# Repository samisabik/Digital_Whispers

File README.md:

## Digital Whispers

In a world populated by an increasing abundance of Artificial Intelligences (AI), it has become more and more important for us to understand the behaviours of our smarter machines. AI promises perfect systems designed to master their functions. As humans, we have imbued these artificial creatures with senses. We have given them the ability to communicate to an ever nearer degree of naturalness; speech and hearing being the most developed. With these efforts, we expect these systems to be as perfect as we have designed them; but what about errors? Beautiful mispronunciation? Hearing loss? Faded meaning? What about the little misunderstandings that makes us human? Can a machine suffer from them and experience them also?

Digital Whispers is an installation that sets seven computers and one human in to a game of Chinese Whispers. The visitor inputs the seed sentence into the “ear” of the first computer and the dialog of ethereal whispers continues in a chain until every machine has had its say. Each computer can hear and talk. It whispers to its neighbour the sentence as it comes into its “ears”. Errors evolves involuntary (or not), creating word chimeras, often resulting in absurd sentences only a robot could have created. The final phrase spoken back to the visitor, most often with surreal overtones, leaves to question the machine as a reflection of humanity.

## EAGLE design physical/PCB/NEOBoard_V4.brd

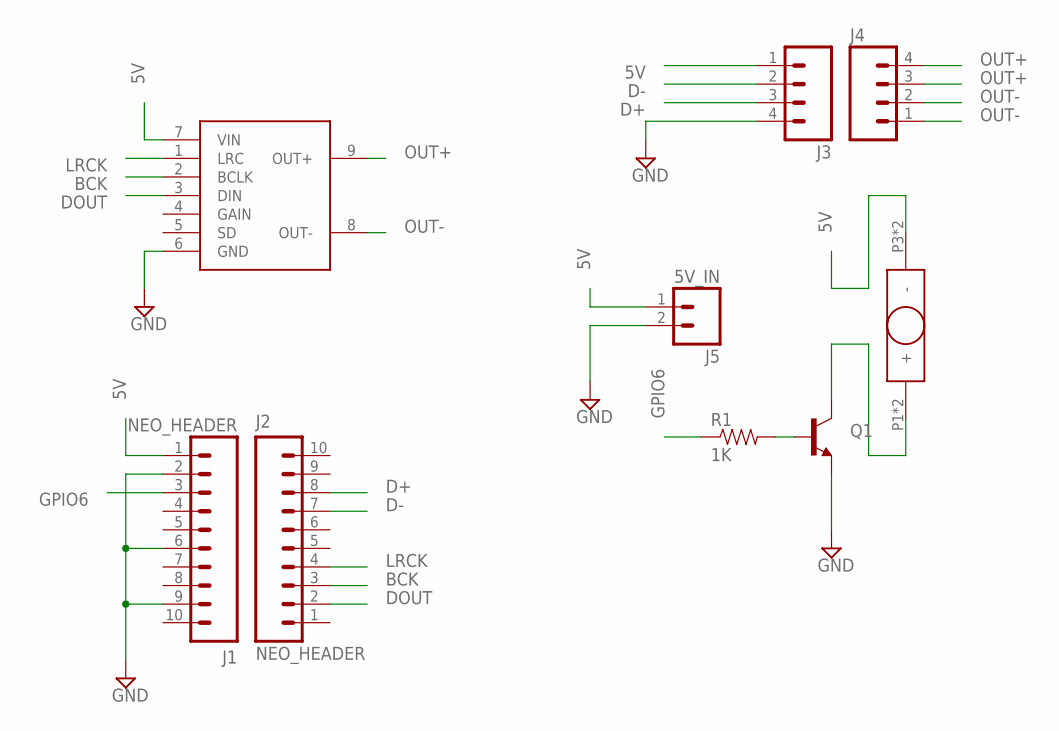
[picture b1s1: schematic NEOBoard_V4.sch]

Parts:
J1, J2: NEO_HEADER; 1X10_NO_SILK
J3, J4: M04NO_SILK_ALL_ROUND; 1X04_NO_SILK_ALL_ROUND
J5: 5V_IN; 1X02_NO_SILK
Q1: TRANSISTOR_NPNTO92; TO-92
R1: 1K; AXIAL-0.3
U$1: I2S_BREAKOUT
U$2: FUSER; FUSE

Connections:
5V: J1.1, J3.1, J5.1, U$1.7 (VIN), U$2.P3 (-), U$2.P4 (-)
BCK: J2.3, U$1.2 (BCLK)
D+: J2.8, J3.3
D-: J2.7, J3.2
DOUT: J2.2, U$1.3 (DIN)
GND: J1.2, J1.6, J1.9, J3.4, J5.2, Q1.1 (E), U$1.6 (GND)
GPIO6: J1.3, R1.P$1 (1)
LRCK: J2.4, U$1.1 (LRC)
unnamed: Q1.2 (B), R1.P$2 (2)
unnamed: Q1.3 (C), U$2.P1 (+), U$2.P2 (+)
OUT+: J4.3, J4.4, U$1.9 (OUT+)
OUT-: J4.1, J4.2, U$1.8 (OUT-)

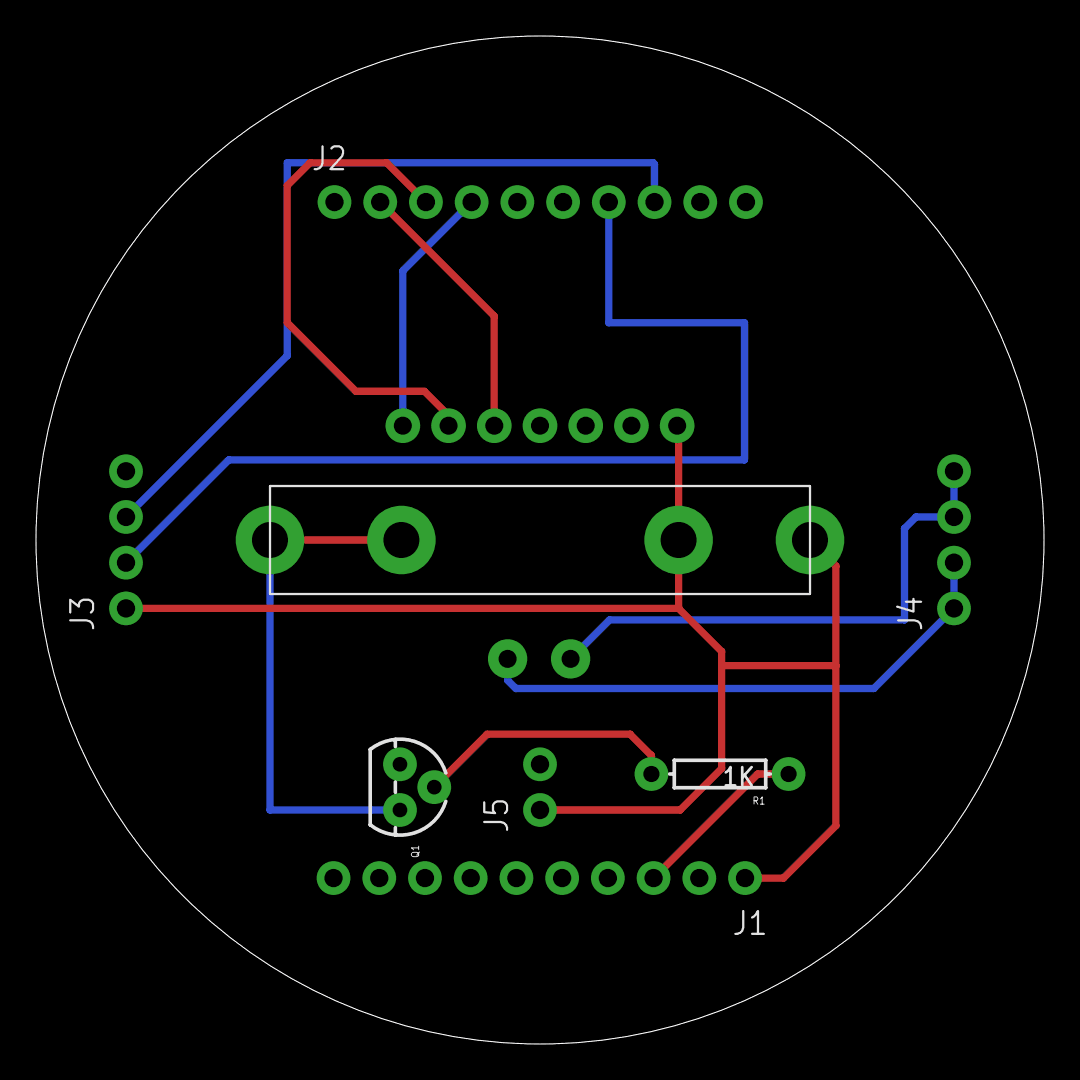
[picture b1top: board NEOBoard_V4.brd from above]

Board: 2 copper layers, 56.0 x 56.0 mm, 9 parts (1 on the bottom side), 12 nets.

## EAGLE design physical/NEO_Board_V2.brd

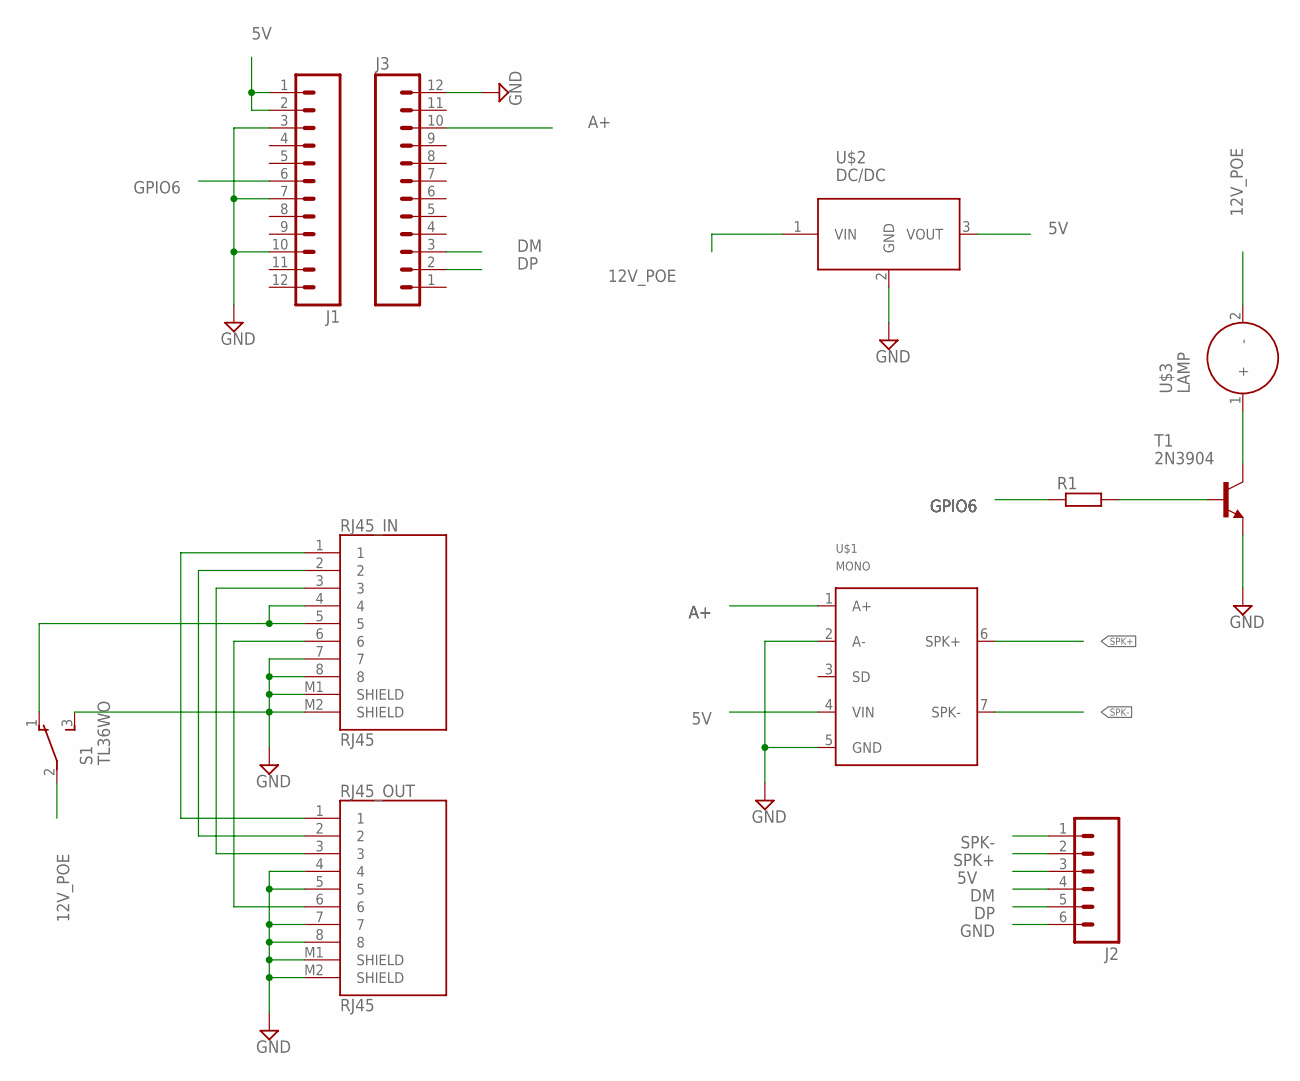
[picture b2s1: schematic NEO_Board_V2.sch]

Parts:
J1, J3: M12PTH; 1X12
J2: M06NO_SILK_FEMALE_PTH; 1X06_NO_SILK
R1: R-EU_0207/10; 0207/10
RJ45_IN, RJ45_OUT: RJ45
S1: TL36WO; TL3XWO
T1: 2N3904; TO92
U$1: MONO; MONO_AMP
U$2: DC/DC
U$3: LAMP

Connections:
5: RJ45_IN.4, RJ45_IN.5, S1.1 (O)
5V: J1.1, J1.2, J2.3, U$1.4 (VIN), U$2.3 (VOUT)
12V_POE: S1.2, U$2.1 (VIN), U$3.2 (-)
A+: J3.10, U$1.1 (A+)
DM: J2.4, J3.3
DP: J2.5, J3.2
GND: J1.3, J1.7, J1.10, J2.6, J3.12, RJ45_IN.7, RJ45_IN.8, RJ45_IN.M1 (SHIELD), RJ45_IN.M2 (SHIELD), RJ45_OUT.4, RJ45_OUT.5, RJ45_OUT.7, RJ45_OUT.8, RJ45_OUT.M1 (SHIELD), RJ45_OUT.M2 (SHIELD), S1.3 (S), T1.3 (E), U$1.2 (A-), U$1.5 (GND), U$2.2 (GND)
GPIO6: J1.6, R1.1
unnamed: R1.2, T1.2 (B)
unnamed: RJ45_IN.6, RJ45_OUT.6
unnamed: T1.1 (C), U$3.1 (+)
unnamed: RJ45_IN.3, RJ45_OUT.3
unnamed: RJ45_IN.2, RJ45_OUT.2
unnamed: RJ45_IN.1, RJ45_OUT.1
SPK+: J2.2, U$1.6 (SPK+)
SPK-: J2.1, U$1.7 (SPK-)

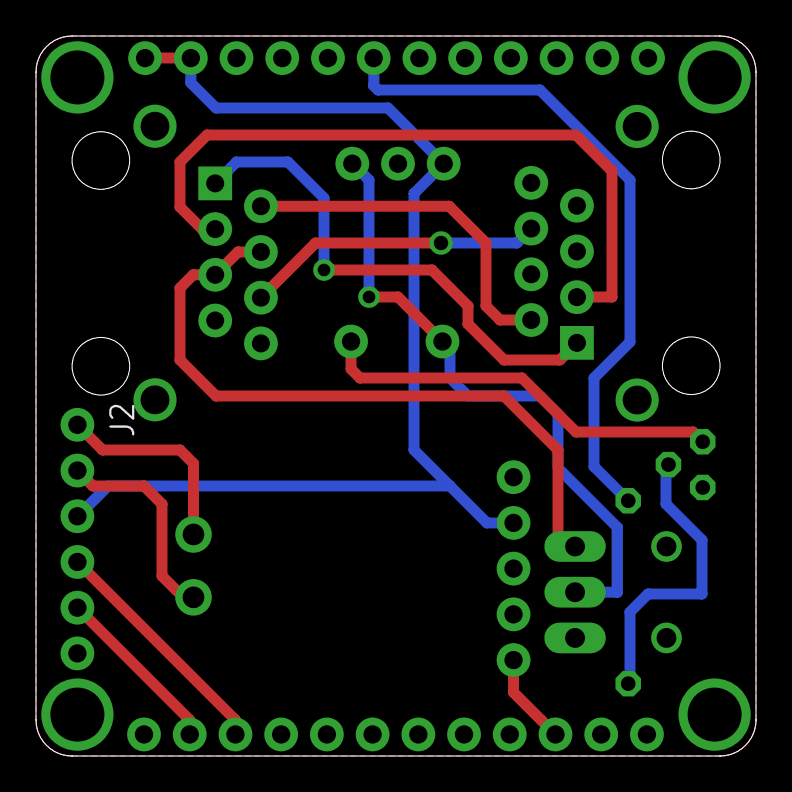
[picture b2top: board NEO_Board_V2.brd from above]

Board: 2 copper layers, 40.0 x 40.0 mm, 11 parts (0 on the bottom side), 16 nets.

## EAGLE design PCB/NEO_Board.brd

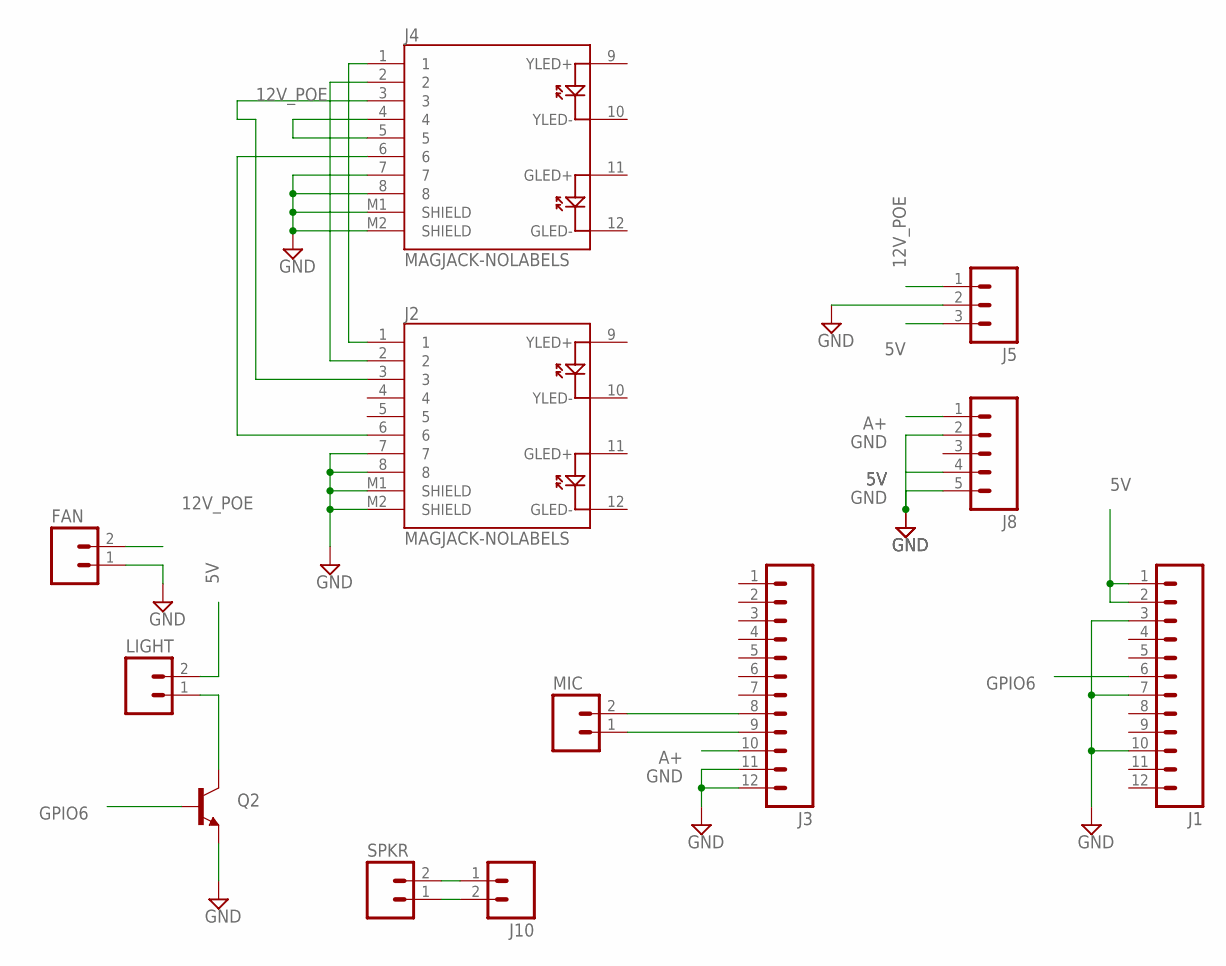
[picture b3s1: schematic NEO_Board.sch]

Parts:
FAN: M02PTH; 1X02
J1, J3: M12PTH; 1X12
J2, J4: MAGJACK-NOLABELS; MAGJACK
J5: M03PTH; 1X03
J8: M05PTH; 1X05
J10: M023.5MM; SCREWTERMINAL-3.5MM-2
LIGHT: M02PTH; 1X02
MIC: M02PTH; 1X02
Q2: TRANSISTOR_NPNP2N2222A; TO-92
SPKR: M02PTH; 1X02

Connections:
5V: J1.1, J1.2, J5.3, J8.4, LIGHT.2
12V_POE: FAN.2, J4.4, J4.5, J5.1
A+: J3.10, J8.1
GND: FAN.1, J1.3, J1.7, J1.10, J2.7, J2.8, J2.M1 (SHIELD), J2.M2 (SHIELD), J3.11, J3.12, J4.7, J4.8, J4.M1 (SHIELD), J4.M2 (SHIELD), J5.2, J8.2, J8.5, Q2.3 (E)
GPIO6: J1.6, Q2.2 (B)
MICN: J3.9, MIC.1
MICP: J3.8, MIC.2
unnamed: J2.1, J4.1
unnamed: J2.2, J4.2
unnamed: J2.3, J4.3
unnamed: J2.6, J4.6
unnamed: LIGHT.1, Q2.1 (C)
unnamed: J10.1, SPKR.2
unnamed: J10.2, SPKR.1

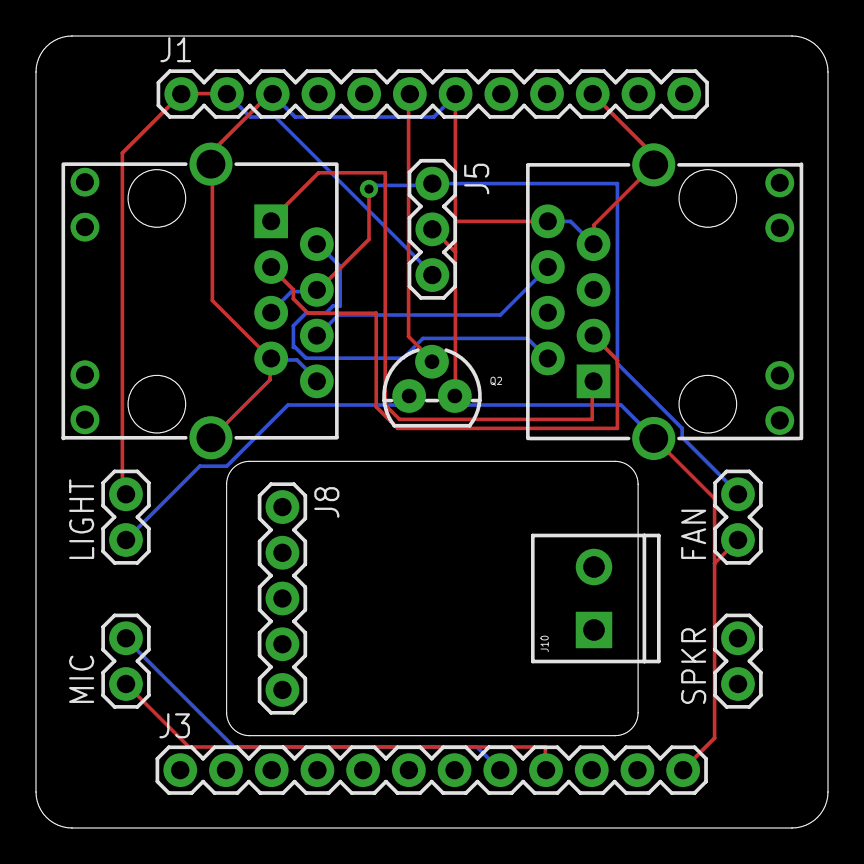
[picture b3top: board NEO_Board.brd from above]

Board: 2 copper layers, 44.0 x 44.0 mm, 12 parts (0 on the bottom side), 14 nets.

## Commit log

2016-06-09 test
2016-06-12 remove slave.py
2016-06-13 clean up
2016-06-13 added voices array // debug function
2016-06-14 clean up + update
2016-06-15 more merge client/server approach
2016-06-16 tweaks
2016-06-17 stuff
2016-06-18 fix server
2016-06-18 add sox
2016-06-21 clean
2016-06-21 cleanup #2
2016-06-27 add UDP/TCP
2016-06-27 sox add
2016-06-29 cleanup // remove pyaudio dep
2016-06-29 added recorder
2016-06-29 pyaudio add
2016-06-29 rm libjack dep
2016-06-30 add alsa.conf
2016-06-30 added setup script
2016-06-30 clean setup.sh
2016-06-30 add prompt input
2016-07-01 add TCP
2016-07-01 rm TCP
2016-07-02 add UDP
2016-07-02 tweak UDP
2016-07-03 tweak
2016-07-04 add hostnamesh
2016-07-15 clean up + PCB
2016-10-14 big update // clean up
2016-10-17 added debug TTS
2016-10-17 added utils in /dev
2016-10-17 gitignore added
2016-10-18 modif setup.sh
2016-10-24 tweak setup.sh
2016-11-03 update physical
2016-11-07 clean up + gitignore /tools
2016-11-10 added config files
2016-11-10 config files
2016-11-10 added asla.conf to setup.sh
2016-11-10 added apt-get
2016-11-10 added gpio
2016-11-21 gitignore + /doc
2017-01-25 spring cleaning
2017-01-25 modif setup.sh for RPi3
2017-01-25 setup.sh
2017-01-25 created /output
2017-01-25 added asound.conf
2017-01-27 add wifi and USB sound
2017-01-27 bla bla
2017-01-27 modif in setup.sh
2017-01-31 big clean up + update setup script
2017-01-31 added empty folder /output
2017-01-31 clean up + gitignore
2017-02-08 modify install.sh
2017-02-08 added a bunch of debug stuff
2017-02-08 auto-rec
2017-02-13 gitignore
2017-02-26 modif install.sh
2017-02-27 modif UDP
2017-02-27 start re-work V2
2017-02-27 modif V2
2017-02-27 V2 work
2017-02-27 last push toight
2017-03-06 massive update V3 // sam gentle is a genius
2017-03-07 move install files to tools and add systemd unit files
2017-03-07 add hostname to install script
2017-03-07 updateall script
2017-03-07 stop Python from buffering log output
2017-03-07 add restart timeout
2017-03-07 make service start after network
2017-03-07 fix client states
2017-03-07 move output to root dir
2017-03-07 make audio paths relative to current dir
2017-03-07 server logging improvements + client linger fix
2017-03-07 added ALSA setup to install.sh
2017-03-07 state machine reliability improvements
2017-03-07 added audio hissing fix
2017-03-07 more generous timeouts
2017-03-07 modified gitignore ++ alsa.cong
2017-03-07 remove Thumbs.db
2017-03-07 messing around with timeout values and socket options
2017-03-07 more delays
2017-03-07 morning clean up
2017-03-08 updated install.sh
2017-03-10 added /output
2017-03-10 update install.sh rm sudo
2017-03-10 moved /output to root
2017-03-10 deleted /main/output
2017-03-10 added noise level
2017-03-13 clean up python -- removed termcolor dep
2017-03-14 added color to server
2017-03-14 color stuff
2017-03-14 color stuff again
2017-03-14 clean up console
2017-03-14 push push push
2017-03-15 added spinner
2017-03-15 fixed bug on client.py
2017-03-16 added .gitignore /iso
2017-03-16 changed location Sydney for IBM
2017-03-16 modif updateall.sh
2017-03-19 added germany loc

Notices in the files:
parts and their libraries:
SparkFun-Connectors: Licensing: Creative Commons ShareAlike 4.0 International - https://creativecommons.org/licenses/by-sa/4.0
